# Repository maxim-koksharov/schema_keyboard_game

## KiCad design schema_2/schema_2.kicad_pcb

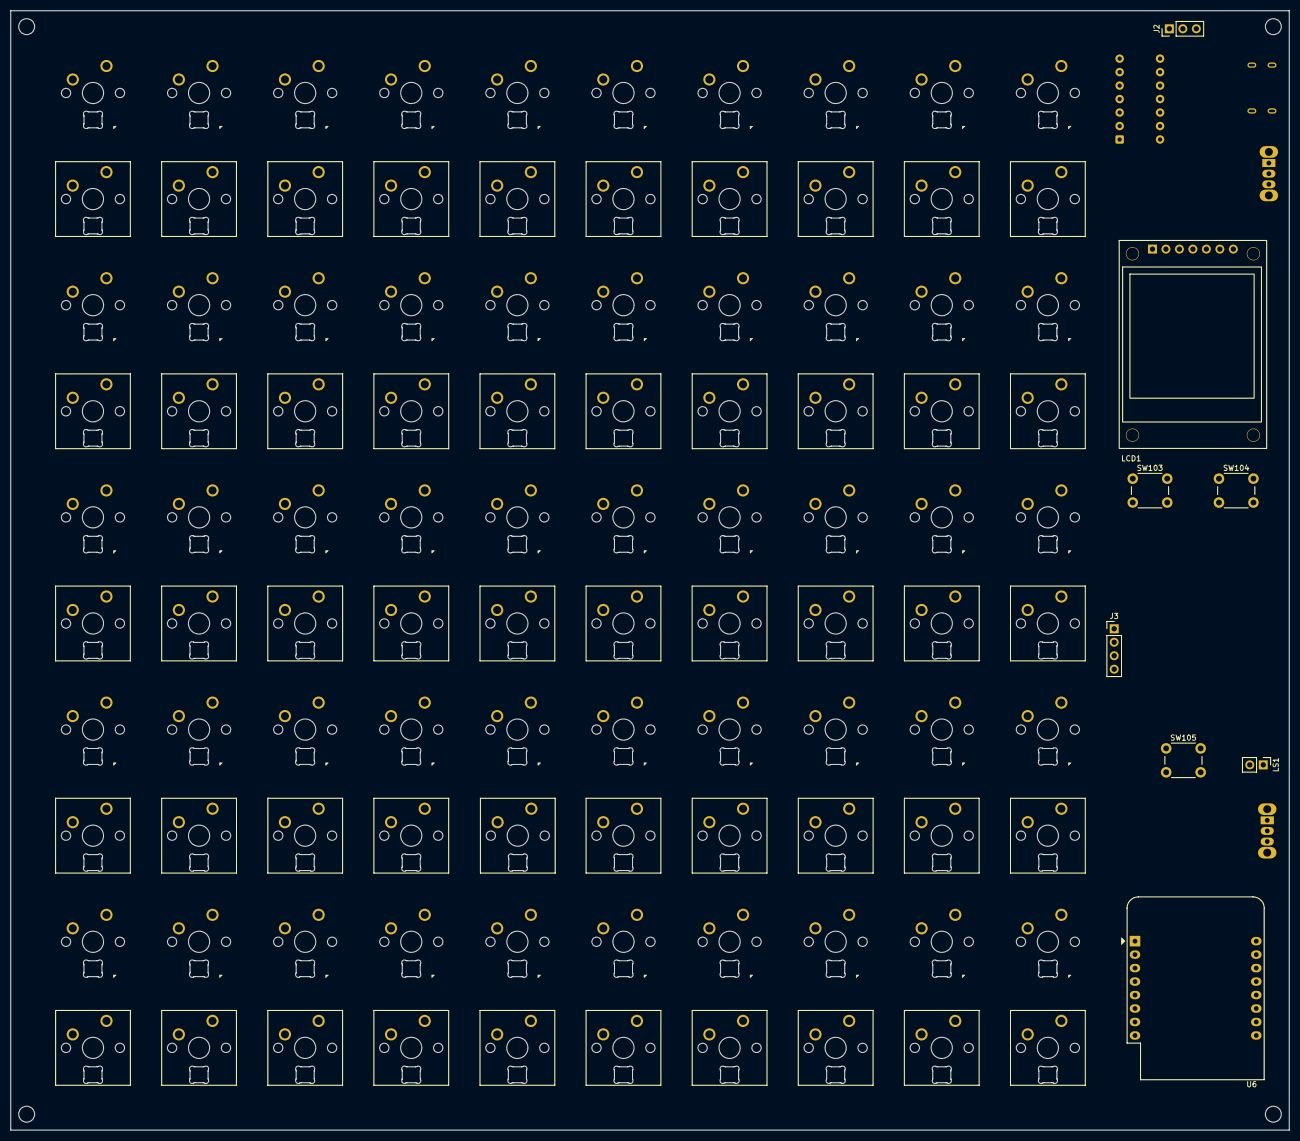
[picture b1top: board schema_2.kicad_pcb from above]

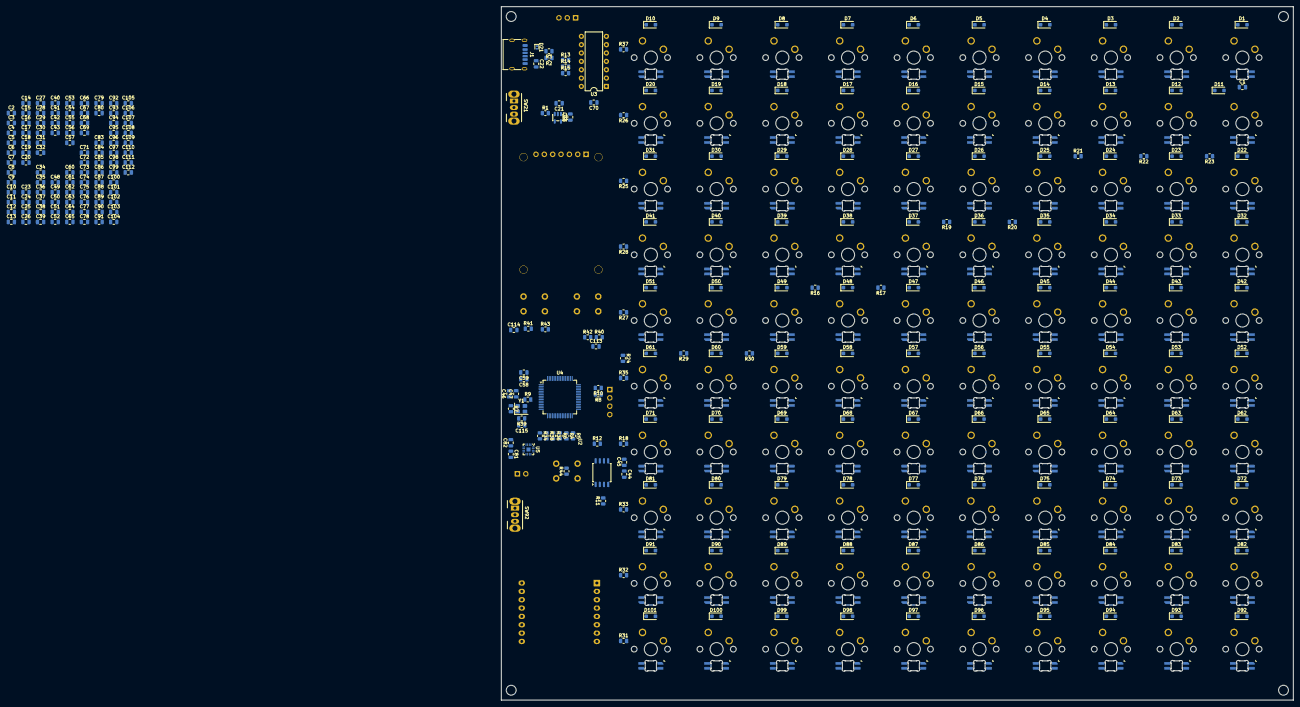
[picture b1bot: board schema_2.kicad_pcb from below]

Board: 2 copper layers, 241.0 x 211.0 mm, 377 parts (269 on the bottom side), 291 nets, no tracks yet.

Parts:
C1, C2, C3, C4, C5, C6, C7, C8, C9, C10, C11, C12, C13, C14, C15, C16, C17, C18, C19, C20, C22, C23, C24, C25, C26, C27, C28, C29, C30, C31, C32, C34, C35, C36, C37, C38, C39, C40, C41, C42, C43, C45, C47, C48, C49, C50, C51, C52, C53, C54, C55, C56, C57, C58, C60, C61, C62, C63, C64, C65, C66, C67, C68, C69, C71, C72, C73, C74, C75, C76, C77, C78, C79, C80, C82, C83, C84, C85, C86, C87, C88, C89, C90, C91, C92, C93, C94, C95, C96, C97, C98, C99, C100, C101, C102, C103, C104, C105, C106, C107, C108, C109, C110, C111, C112, C113, C114, C115: 100n; C_0805_2012Metric
C21, C33: 1u; C_0805_2012Metric
C44, C46, C81: 10u; C_0805_2012Metric
C59: 4.7u; C_0805_2012Metric
C70: 100p; C_0805_2012Metric
D1, D2, D3, D4, D5, D6, D7, D8, D9, D10, D11, D12, D13, D14, D15, D16, D17, D18, D19, D20, D22, D23, D24, D25, D26, D27, D28, D29, D30, D31, D32, D33, D34, D35, D36, D37, D38, D39, D40, D41, D42, D43, D44, D45, D46, D47, D48, D49, D50, D51, D52, D53, D54, D55, D56, D57, D58, D59, D60, D61, D62, D63, D64, D65, D66, D67, D68, D69, D70, D71, D72, D73, D74, D75, D76, D77, D78, D79, D80, D81, D82, D83, D84, D85, D86, D87, D88, D89, D90, D91, D92, D93, D94, D95, D96, D97, D98, D99, D100, D101: SM4007PL; D_SOD-123F
D21: H5VL10B; D_SOD-882D
J1: USB_C_Receptacle_PowerOnly_6P; USB_C_Receptacle_HRO_TYPE-C-31-M-17
J2: Conn_01x03_Pin; PinHeader_1x03_P2.54mm_Vertical
J3: Conn_01x04_Pin; PinHeader_1x04_P2.54mm_Vertical
LCD1: ST7789_1.3_240x240_LCD_Module
LS1: Speaker; PinHeader_1x02_P2.54mm_Vertical
R1, R42, R43, R44: 1k; R_0805_2012Metric
R2, R3, R13, R14, R15: 5.1k; R_0805_2012Metric
R4, R5, R6, R8, R9, R10, R34, R36, R38: 22; R_0805_2012Metric
R7, R11, R12, R39, R40, R41: 10k; R_0805_2012Metric
R16, R17, R18, R19, R20, R21, R22, R23, R24, R25, R26, R27, R28, R29, R30, R31, R32, R33, R35, R37: 220; R_0805_2012Metric
SW1, SW2, SW3, SW4, SW5, SW6, SW7, SW8, SW9, SW10, SW22, SW23, SW24, SW25, SW26, SW27, SW28, SW29, SW30, SW31, SW42, SW43, SW44, SW45, SW46, SW47, SW48, SW49, SW50, SW51, SW62, SW63, SW64, SW65, SW66, SW67, SW68, SW69, SW70, SW71, SW82, SW83, SW84, SW85, SW86, SW87, SW88, SW89, SW90, SW91: SW_MX_1u_SK6812MINI-E
SW11, SW12, SW13, SW14, SW15, SW16, SW17, SW18, SW19, SW20, SW32, SW33, SW34, SW35, SW36, SW37, SW38, SW39, SW40, SW41, SW52, SW53, SW54, SW55, SW56, SW57, SW58, SW59, SW60, SW61, SW72, SW73, SW74, SW75, SW76, SW77, SW78, SW79, SW80, SW81, SW93, SW94, SW95, SW96, SW97, SW98, SW99, SW100, SW101, SW102: SW_MX_1u_SK6812MINI-E_ROTATE
SW21, SW92: SK12D07VG3; SW_Slide_SPDT_Angled_CK_OS102011MA1Q
SW103, SW104, SW105: SW_Push; SW_PUSH_6mm
U1: AP2112K-3.3; SOT-23-5
U2: W25Q128JVS; SOIC-8_5.3x5.3mm_P1.27mm
U3: 74AHCT125; DIP-14_W7.62mm
U4: STM32G070RBTx; LQFP-64_10x10mm_P0.5mm
U5: MAX98357A; TQFN-16-1EP_3x3mm_P0.5mm_EP1.23x1.23mm
U6: WEMOS_D1_mini; WEMOS_D1_mini_light
Y1: SX3M8.000M20F30TNN; Crystal_SMD_3225-4Pin_3.2x2.5mm

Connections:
+3V3: C33.1, C44.1, C45.1, C46.1, C47.1, C58.1, C59.1, J2.2, J3.3, LCD1.2 (VCC), R7.1, R11.1, R12.1, R39.2, R40.2, R41.2, U1.5 (VOUT), U2.8 (VCC), U4.8 (VDD), Y1.4 (VDD)
+5V: C21.1, C70.2, C81.1, C82.1, R1.1, SW21.1 (A), U1.1 (VIN), U3.14 (VCC), U5.7 (VDD), U5.8 (VDD)
+5VP: C1.1, C2.1, C3.1, C4.1, C5.1, C6.1, C7.1, C8.1, C9.1, C10.1, C11.1, C12.1, C13.1, C14.1, C15.1, C16.1, C17.1, C18.1, C19.1, C20.1, C22.1, C23.1, C24.1, C25.1, C26.1, C27.1, C28.1, C29.1, C30.1, C31.1, C32.1, C34.1, C35.1, C36.1, C37.1, C38.1, C39.1, C40.1, C41.1, C42.1, C43.1, C48.1, C49.1, C50.1, C51.1, C52.1, C53.1, C54.1, C55.1, C56.1, C57.1, C60.1, C61.1, C62.1, C63.1, C64.1, C65.1, C66.1, C67.1, C68.1, C69.1, C71.1, C72.1, C73.1, C74.1, C75.1, C76.1, C77.1, C78.1, C79.1, C80.1, C83.1, C84.1, C85.1, C86.1, C87.1, C88.1, C89.1, C90.1, C91.1, C92.1, C93.1, C94.1, C95.1, C96.1, C97.1, C98.1, C99.1, C100.1, C101.1, C102.1, C103.1, C104.1, C105.1, C106.1, C107.1, C108.1, C109.1, C110.1, C111.1, C112.1, D21.2 (A2), J1.A9 (VBUS), J1.B9 (VBUS), J2.1, R13.1, R14.1, R15.1, SW1.1 (VDD), SW2.1 (VDD), SW3.1 (VDD), SW4.1 (VDD), SW5.1 (VDD), SW6.1 (VDD), SW7.1 (VDD), SW8.1 (VDD), SW9.1 (VDD), SW10.1 (VDD), SW11.1 (VDD), SW12.1 (VDD), SW13.1 (VDD), SW14.1 (VDD), SW15.1 (VDD), SW16.1 (VDD), SW17.1 (VDD), SW18.1 (VDD), SW19.1 (VDD), SW20.1 (VDD), SW21.2 (B), SW22.1 (VDD), SW23.1 (VDD), SW24.1 (VDD), SW25.1 (VDD), SW26.1 (VDD), SW27.1 (VDD), SW28.1 (VDD), SW29.1 (VDD), SW30.1 (VDD), SW31.1 (VDD), SW32.1 (VDD), SW33.1 (VDD), SW34.1 (VDD), SW35.1 (VDD), SW36.1 (VDD), SW37.1 (VDD), SW38.1 (VDD), SW39.1 (VDD), SW40.1 (VDD), SW41.1 (VDD), SW42.1 (VDD), SW43.1 (VDD), SW44.1 (VDD), SW45.1 (VDD), SW46.1 (VDD), SW47.1 (VDD), SW48.1 (VDD), SW49.1 (VDD), SW50.1 (VDD), SW51.1 (VDD), SW52.1 (VDD), SW53.1 (VDD), SW54.1 (VDD), SW55.1 (VDD), SW56.1 (VDD), SW57.1 (VDD), SW58.1 (VDD), SW59.1 (VDD), SW60.1 (VDD), SW61.1 (VDD), SW62.1 (VDD), SW63.1 (VDD), SW64.1 (VDD), SW65.1 (VDD), SW66.1 (VDD), SW67.1 (VDD), SW68.1 (VDD), SW69.1 (VDD), SW70.1 (VDD), SW71.1 (VDD), SW72.1 (VDD), SW73.1 (VDD), SW74.1 (VDD), SW75.1 (VDD), SW76.1 (VDD), SW77.1 (VDD), SW78.1 (VDD), SW79.1 (VDD), SW80.1 (VDD), SW81.1 (VDD), SW82.1 (VDD), SW83.1 (VDD), SW84.1 (VDD), SW85.1 (VDD), SW86.1 (VDD), SW87.1 (VDD), SW88.1 (VDD), SW89.1 (VDD), SW90.1 (VDD), SW91.1 (VDD), SW92.2 (B), SW93.1 (VDD), SW94.1 (VDD), SW95.1 (VDD), SW96.1 (VDD), SW97.1 (VDD), SW98.1 (VDD), SW99.1 (VDD), SW100.1 (VDD), SW101.1 (VDD), SW102.1 (VDD)
/audio_bclk: R36.1, U4.22 (PA5)
/audio_din: R34.1, U4.19 (PA2)
/audio_lrclk: R38.1, U4.21 (PA4)
/audio_mode: U4.23 (PA6), U5.4 (~SD_MODE)
/blk_lcd: LCD1.7 (BLK), U4.62 (PB8)
/col_1: D1.1 (K), D11.1 (K), D22.1 (K), D32.1 (K), D42.1 (K), D52.1 (K), D62.1 (K), D72.1 (K), D82.1 (K), D92.1 (K), R23.1
/col_2: D2.1 (K), D12.1 (K), D23.1 (K), D33.1 (K), D43.1 (K), D53.1 (K), D63.1 (K), D73.1 (K), D83.1 (K), D93.1 (K), R22.1
/col_3: D3.1 (K), D13.1 (K), D24.1 (K), D34.1 (K), D44.1 (K), D54.1 (K), D64.1 (K), D74.1 (K), D84.1 (K), D94.1 (K), R21.1
/col_4: D4.1 (K), D14.1 (K), D25.1 (K), D35.1 (K), D45.1 (K), D55.1 (K), D65.1 (K), D75.1 (K), D85.1 (K), D95.1 (K), R20.1
/col_5: D5.1 (K), D15.1 (K), D26.1 (K), D36.1 (K), D46.1 (K), D56.1 (K), D66.1 (K), D76.1 (K), D86.1 (K), D96.1 (K), R19.1
/col_6: D6.1 (K), D16.1 (K), D27.1 (K), D37.1 (K), D47.1 (K), D57.1 (K), D67.1 (K), D77.1 (K), D87.1 (K), D97.1 (K), R17.1
/col_7: D7.1 (K), D17.1 (K), D28.1 (K), D38.1 (K), D48.1 (K), D58.1 (K), D68.1 (K), D78.1 (K), D88.1 (K), D98.1 (K), R16.1
/col_8: D8.1 (K), D18.1 (K), D29.1 (K), D39.1 (K), D49.1 (K), D59.1 (K), D69.1 (K), D79.1 (K), D89.1 (K), D99.1 (K), R30.1
/col_9: D9.1 (K), D19.1 (K), D30.1 (K), D40.1 (K), D50.1 (K), D60.1 (K), D70.1 (K), D80.1 (K), D90.1 (K), D100.1 (K), R29.1
/col_10: D10.1 (K), D20.1 (K), D31.1 (K), D41.1 (K), D51.1 (K), D61.1 (K), D71.1 (K), D81.1 (K), D91.1 (K), D101.1 (K), R24.2
/dc_lcd: LCD1.6 (DC), U4.59 (PB5)
/esp_reset: U4.16 (PC3), U6.1 (~RST)
/esp_uart_rx: U4.17 (PA0), U6.15 (RX)
/esp_uart_tx: U4.18 (PA1), U6.16 (TX)
/key_1: C113.1, R40.1, R42.2, U4.1 (PC11)
/key_2: C114.1, R41.1, R43.2, U4.2 (PC12)
/led_1: SW9.4 (DIN), SW10.2 (DOUT)
/led_2: SW8.4 (DIN), SW9.2 (DOUT)
/led_3: SW7.4 (DIN), SW8.2 (DOUT)
/led_4: SW6.4 (DIN), SW7.2 (DOUT)
/led_5: SW5.4 (DIN), SW6.2 (DOUT)
/led_6: SW4.4 (DIN), SW5.2 (DOUT)
/led_7: SW3.4 (DIN), SW4.2 (DOUT)
/led_8: SW2.4 (DIN), SW3.2 (DOUT)
/led_9: SW1.4 (DIN), SW2.2 (DOUT)
/led_10: SW1.2 (DOUT), SW11.4 (DIN)
/led_11: SW11.2 (DOUT), SW12.4 (DIN)
/led_12: SW12.2 (DOUT), SW13.4 (DIN)
/led_13: SW13.2 (DOUT), SW14.4 (DIN)
/led_14: SW14.2 (DOUT), SW15.4 (DIN)
/led_15: SW15.2 (DOUT), SW16.4 (DIN)
/led_16: SW16.2 (DOUT), SW17.4 (DIN)
/led_17: SW17.2 (DOUT), SW18.4 (DIN)
/led_18: SW18.2 (DOUT), SW19.4 (DIN)
/led_19: SW19.2 (DOUT), SW20.4 (DIN)
/led_20: SW20.2 (DOUT), SW31.4 (DIN)
/led_21: SW30.4 (DIN), SW31.2 (DOUT)
/led_22: SW29.4 (DIN), SW30.2 (DOUT)
/led_23: SW28.4 (DIN), SW29.2 (DOUT)
/led_24: SW27.4 (DIN), SW28.2 (DOUT)
/led_25: SW26.4 (DIN), SW27.2 (DOUT)
/led_26: SW25.4 (DIN), SW26.2 (DOUT)
/led_27: SW24.4 (DIN), SW25.2 (DOUT)
/led_28: SW23.4 (DIN), SW24.2 (DOUT)
/led_29: SW22.4 (DIN), SW23.2 (DOUT)
/led_30: SW22.2 (DOUT), SW32.4 (DIN)
/led_31: SW32.2 (DOUT), SW33.4 (DIN)
/led_32: SW33.2 (DOUT), SW34.4 (DIN)
/led_33: SW34.2 (DOUT), SW35.4 (DIN)
/led_34: SW35.2 (DOUT), SW36.4 (DIN)
/led_35: SW36.2 (DOUT), SW37.4 (DIN)
/led_36: SW37.2 (DOUT), SW38.4 (DIN)
/led_37: SW38.2 (DOUT), SW39.4 (DIN)
/led_38: SW39.2 (DOUT), SW40.4 (DIN)
/led_39: SW40.2 (DOUT), SW41.4 (DIN)
/led_40: SW41.2 (DOUT), SW51.4 (DIN)
/led_41: SW50.4 (DIN), SW51.2 (DOUT)
/led_42: SW49.4 (DIN), SW50.2 (DOUT)
/led_43: SW48.4 (DIN), SW49.2 (DOUT)
/led_44: SW47.4 (DIN), SW48.2 (DOUT)
/led_45: SW46.4 (DIN), SW47.2 (DOUT)
/led_46: SW45.4 (DIN), SW46.2 (DOUT)
/led_47: SW44.4 (DIN), SW45.2 (DOUT)
/led_48: SW43.4 (DIN), SW44.2 (DOUT)
/led_49: SW42.4 (DIN), SW43.2 (DOUT)
/led_50: SW42.2 (DOUT), SW52.4 (DIN)
/led_51: SW52.2 (DOUT), SW53.4 (DIN)
/led_52: SW53.2 (DOUT), SW54.4 (DIN)
/led_53: SW54.2 (DOUT), SW55.4 (DIN)
/led_54: SW55.2 (DOUT), SW56.4 (DIN)
/led_55: SW56.2 (DOUT), SW57.4 (DIN)
/led_56: SW57.2 (DOUT), SW58.4 (DIN)
/led_57: SW58.2 (DOUT), SW59.4 (DIN)
/led_58: SW59.2 (DOUT), SW60.4 (DIN)
/led_59: SW60.2 (DOUT), SW61.4 (DIN)
/led_60: SW61.2 (DOUT), SW71.4 (DIN)
/led_61: SW70.4 (DIN), SW71.2 (DOUT)
/led_62: SW69.4 (DIN), SW70.2 (DOUT)
/led_63: SW68.4 (DIN), SW69.2 (DOUT)
/led_64: SW67.4 (DIN), SW68.2 (DOUT)
/led_65: SW66.4 (DIN), SW67.2 (DOUT)
/led_66: SW65.4 (DIN), SW66.2 (DOUT)
/led_67: SW64.4 (DIN), SW65.2 (DOUT)
/led_68: SW63.4 (DIN), SW64.2 (DOUT)
/led_69: SW62.4 (DIN), SW63.2 (DOUT)
/led_70: SW62.2 (DOUT), SW72.4 (DIN)
/led_71: SW72.2 (DOUT), SW73.4 (DIN)
/led_72: SW73.2 (DOUT), SW74.4 (DIN)
/led_73: SW74.2 (DOUT), SW75.4 (DIN)
/led_74: SW75.2 (DOUT), SW76.4 (DIN)
/led_75: SW76.2 (DOUT), SW77.4 (DIN)
/led_76: SW77.2 (DOUT), SW78.4 (DIN)
/led_77: SW78.2 (DOUT), SW79.4 (DIN)
/led_78: SW79.2 (DOUT), SW80.4 (DIN)
/led_79: SW80.2 (DOUT), SW81.4 (DIN)
/led_80: SW81.2 (DOUT), SW91.4 (DIN)
/led_81: SW90.4 (DIN), SW91.2 (DOUT)
/led_82: SW89.4 (DIN), SW90.2 (DOUT)
/led_83: SW88.4 (DIN), SW89.2 (DOUT)
/led_84: SW87.4 (DIN), SW88.2 (DOUT)
/led_85: SW86.4 (DIN), SW87.2 (DOUT)
/led_86: SW85.4 (DIN), SW86.2 (DOUT)
/led_87: SW84.4 (DIN), SW85.2 (DOUT)
/led_88: SW83.4 (DIN), SW84.2 (DOUT)
/led_89: SW82.4 (DIN), SW83.2 (DOUT)
/led_90: SW82.2 (DOUT), SW93.4 (DIN)
/led_91: SW93.2 (DOUT), SW94.4 (DIN)
/led_92: SW94.2 (DOUT), SW95.4 (DIN)
/led_93: SW95.2 (DOUT), SW96.4 (DIN)
/led_94: SW96.2 (DOUT), SW97.4 (DIN)
/led_95: SW97.2 (DOUT), SW98.4 (DIN)
/led_96: SW98.2 (DOUT), SW99.4 (DIN)
/led_97: SW99.2 (DOUT), SW100.4 (DIN)
/led_98: SW100.2 (DOUT), SW101.4 (DIN)
/led_99: SW101.2 (DOUT), SW102.4 (DIN)
/mcu_clk: R9.2, U4.10 (PF0)
/reset_lcd: LCD1.5 (RES), U4.58 (PB4)
/rgb_data_3V: U3.2, U4.64 (PC10)
/rgb_data_5V: SW10.4 (DIN), U3.3
/row_1: R37.2, SW1.5 (SW_1), SW2.5 (SW_1), SW3.5 (SW_1), SW4.5 (SW_1), SW5.5 (SW_1), SW6.5 (SW_1), SW7.5 (SW_1), SW8.5 (SW_1), SW9.5 (SW_1), SW10.5 (SW_1)
/row_2: R26.1, SW11.5 (SW_1), SW12.5 (SW_1), SW13.5 (SW_1), SW14.5 (SW_1), SW15.5 (SW_1), SW16.5 (SW_1), SW17.5 (SW_1), SW18.5 (SW_1), SW19.5 (SW_1), SW20.5 (SW_1)
/row_3: R25.1, SW22.5 (SW_1), SW23.5 (SW_1), SW24.5 (SW_1), SW25.5 (SW_1), SW26.5 (SW_1), SW27.5 (SW_1), SW28.5 (SW_1), SW29.5 (SW_1), SW30.5 (SW_1), SW31.5 (SW_1)
/row_4: R28.1, SW32.5 (SW_1), SW33.5 (SW_1), SW34.5 (SW_1), SW35.5 (SW_1), SW36.5 (SW_1), SW37.5 (SW_1), SW38.5 (SW_1), SW39.5 (SW_1), SW40.5 (SW_1), SW41.5 (SW_1)
/row_5: R27.1, SW42.5 (SW_1), SW43.5 (SW_1), SW44.5 (SW_1), SW45.5 (SW_1), SW46.5 (SW_1), SW47.5 (SW_1), SW48.5 (SW_1), SW49.5 (SW_1), SW50.5 (SW_1), SW51.5 (SW_1)
/row_6: R35.2, SW52.5 (SW_1), SW53.5 (SW_1), SW54.5 (SW_1), SW55.5 (SW_1), SW56.5 (SW_1), SW57.5 (SW_1), SW58.5 (SW_1), SW59.5 (SW_1), SW60.5 (SW_1), SW61.5 (SW_1)
/row_7: R18.2, SW62.5 (SW_1), SW63.5 (SW_1), SW64.5 (SW_1), SW65.5 (SW_1), SW66.5 (SW_1), SW67.5 (SW_1), SW68.5 (SW_1), SW69.5 (SW_1), SW70.5 (SW_1), SW71.5 (SW_1)
/row_8: R33.2, SW72.5 (SW_1), SW73.5 (SW_1), SW74.5 (SW_1), SW75.5 (SW_1), SW76.5 (SW_1), SW77.5 (SW_1), SW78.5 (SW_1), SW79.5 (SW_1), SW80.5 (SW_1), SW81.5 (SW_1)
/row_9: R32.2, SW82.5 (SW_1), SW83.5 (SW_1), SW84.5 (SW_1), SW85.5 (SW_1), SW86.5 (SW_1), SW87.5 (SW_1), SW88.5 (SW_1), SW89.5 (SW_1), SW90.5 (SW_1), SW91.5 (SW_1)
/row_10: R31.2, SW93.5 (SW_1), SW94.5 (SW_1), SW95.5 (SW_1), SW96.5 (SW_1), SW97.5 (SW_1), SW98.5 (SW_1), SW99.5 (SW_1), SW100.5 (SW_1), SW101.5 (SW_1), SW102.5 (SW_1)
/spi_clk_lcd: LCD1.3 (SCK), U4.57 (PB3)
/spi_data_lcd: LCD1.4 (SDA), U4.60 (PB6)
/spi_mem_clk: R4.1, U4.30 (PB10)
/spi_mem_cs: U2.1 (~CS), U4.32 (PB12)
/spi_mem_miso: R6.1, U4.29 (PB2)
/spi_mem_mosi: R5.1, U4.31 (PB11)
/stm32_reset: C115.1, R39.1, R44.2, U4.12 (NRST)
/swclk: R10.2, U4.46 (PA14)
/swdio: R8.2, U4.45 (PA13)
GND: C1.2, C2.2, C3.2, C4.2, C5.2, C6.2, C7.2, C8.2, C9.2, C10.2, C11.2, C12.2, C13.2, C14.2, C15.2, C16.2, C17.2, C18.2, C19.2, C20.2, C21.2, C22.2, C23.2, C24.2, C25.2, C26.2, C27.2, C28.2, C29.2, C30.2, C31.2, C32.2, C33.2, C34.2, C35.2, C36.2, C37.2, C38.2, C39.2, C40.2, C41.2, C42.2, C43.2, C44.2, C45.2, C46.2, C47.2, C48.2, C49.2, C50.2, C51.2, C52.2, C53.2, C54.2, C55.2, C56.2, C57.2, C58.2, C59.2, C60.2, C61.2, C62.2, C63.2, C64.2, C65.2, C66.2, C67.2, C68.2, C69.2, C70.1, C71.2, C72.2, C73.2, C74.2, C75.2, C76.2, C77.2, C78.2, C79.2, C80.2, C81.2, C82.2, C83.2, C84.2, C85.2, C86.2, C87.2, C88.2, C89.2, C90.2, C91.2, C92.2, C93.2, C94.2, C95.2, C96.2, C97.2, C98.2, C99.2, C100.2, C101.2, C102.2, C103.2, C104.2, C105.2, C106.2, C107.2, C108.2, C109.2, C110.2, C111.2, C112.2, C113.2, C114.2, C115.2, D21.1 (A1), J1.A12 (GND), J1.B12 (GND), J2.3, J3.4, LCD1.1 (GND), R2.1, R3.1, SW1.3 (VSS), SW2.3 (VSS), SW3.3 (VSS), SW4.3 (VSS), SW5.3 (VSS), SW6.3 (VSS), SW7.3 (VSS), SW8.3 (VSS), SW9.3 (VSS), SW10.3 (VSS), SW11.3 (VSS), SW12.3 (VSS), SW13.3 (VSS), SW14.3 (VSS), SW15.3 (VSS), SW16.3 (VSS), SW17.3 (VSS), SW18.3 (VSS), SW19.3 (VSS), SW20.3 (VSS), SW22.3 (VSS), SW23.3 (VSS), SW24.3 (VSS), SW25.3 (VSS), SW26.3 (VSS), SW27.3 (VSS), SW28.3 (VSS), SW29.3 (VSS), SW30.3 (VSS), SW31.3 (VSS), SW32.3 (VSS), SW33.3 (VSS), SW34.3 (VSS), SW35.3 (VSS), SW36.3 (VSS), SW37.3 (VSS), SW38.3 (VSS), SW39.3 (VSS), SW40.3 (VSS), SW41.3 (VSS), SW42.3 (VSS), SW43.3 (VSS), SW44.3 (VSS), SW45.3 (VSS), SW46.3 (VSS), SW47.3 (VSS), SW48.3 (VSS), SW49.3 (VSS), SW50.3 (VSS), SW51.3 (VSS), SW52.3 (VSS), SW53.3 (VSS), SW54.3 (VSS), SW55.3 (VSS), SW56.3 (VSS), SW57.3 (VSS), SW58.3 (VSS), SW59.3 (VSS), SW60.3 (VSS), SW61.3 (VSS), SW62.3 (VSS), SW63.3 (VSS), SW64.3 (VSS), SW65.3 (VSS), SW66.3 (VSS), SW67.3 (VSS), SW68.3 (VSS), SW69.3 (VSS), SW70.3 (VSS), SW71.3 (VSS), SW72.3 (VSS), SW73.3 (VSS), SW74.3 (VSS), SW75.3 (VSS), SW76.3 (VSS), SW77.3 (VSS), SW78.3 (VSS), SW79.3 (VSS), SW80.3 (VSS), SW81.3 (VSS), SW82.3 (VSS), SW83.3 (VSS), SW84.3 (VSS), SW85.3 (VSS), SW86.3 (VSS), SW87.3 (VSS), SW88.3 (VSS), SW89.3 (VSS), SW90.3 (VSS), SW91.3 (VSS), SW93.3 (VSS), SW94.3 (VSS), SW95.3 (VSS), SW96.3 (VSS), SW97.3 (VSS), SW98.3 (VSS), SW99.3 (VSS), SW100.3 (VSS), SW101.3 (VSS), SW102.3 (VSS), SW103.1, SW104.1, SW105.1, U1.2 (GND), U2.4 (GND), U3.1, U3.7 (GND), U4.9 (VSS), U5.2 (GAIN_SLOT), U5.3 (GND), U5.11 (GND), U5.15 (GND), U5.17 (PAD), U6.10 (GND), Y1.2 (GND)
unnamed: D1.2 (A), SW1.6 (SW_2)
unnamed: D2.2 (A), SW2.6 (SW_2)
unnamed: D3.2 (A), SW3.6 (SW_2)
unnamed: D4.2 (A), SW4.6 (SW_2)
unnamed: D5.2 (A), SW5.6 (SW_2)
unnamed: D6.2 (A), SW6.6 (SW_2)
unnamed: D7.2 (A), SW7.6 (SW_2)
unnamed: D8.2 (A), SW8.6 (SW_2)
unnamed: D9.2 (A), SW9.6 (SW_2)
unnamed: D10.2 (A), SW10.6 (SW_2)
unnamed: D11.2 (A), SW11.6 (SW_2)
unnamed: D12.2 (A), SW12.6 (SW_2)
unnamed: D13.2 (A), SW13.6 (SW_2)
unnamed: D14.2 (A), SW14.6 (SW_2)
unnamed: D15.2 (A), SW15.6 (SW_2)
unnamed: D16.2 (A), SW16.6 (SW_2)
unnamed: D17.2 (A), SW17.6 (SW_2)
unnamed: D18.2 (A), SW18.6 (SW_2)
unnamed: D19.2 (A), SW19.6 (SW_2)
unnamed: D20.2 (A), SW20.6 (SW_2)
unnamed: D22.2 (A), SW22.6 (SW_2)
unnamed: D23.2 (A), SW23.6 (SW_2)
unnamed: D24.2 (A), SW24.6 (SW_2)
unnamed: D25.2 (A), SW25.6 (SW_2)
unnamed: D26.2 (A), SW26.6 (SW_2)
unnamed: D27.2 (A), SW27.6 (SW_2)
unnamed: D28.2 (A), SW28.6 (SW_2)
unnamed: D29.2 (A), SW29.6 (SW_2)
unnamed: D30.2 (A), SW30.6 (SW_2)
unnamed: D31.2 (A), SW31.6 (SW_2)
unnamed: D32.2 (A), SW32.6 (SW_2)
unnamed: D33.2 (A), SW33.6 (SW_2)
unnamed: D34.2 (A), SW34.6 (SW_2)
unnamed: D35.2 (A), SW35.6 (SW_2)
unnamed: D36.2 (A), SW36.6 (SW_2)
unnamed: D37.2 (A), SW37.6 (SW_2)
unnamed: D38.2 (A), SW38.6 (SW_2)
unnamed: D39.2 (A), SW39.6 (SW_2)
unnamed: D40.2 (A), SW40.6 (SW_2)
unnamed: D41.2 (A), SW41.6 (SW_2)
unnamed: D42.2 (A), SW42.6 (SW_2)
unnamed: D43.2 (A), SW43.6 (SW_2)
unnamed: D44.2 (A), SW44.6 (SW_2)
unnamed: D45.2 (A), SW45.6 (SW_2)
unnamed: D46.2 (A), SW46.6 (SW_2)
unnamed: D47.2 (A), SW47.6 (SW_2)
unnamed: D48.2 (A), SW48.6 (SW_2)
unnamed: D49.2 (A), SW49.6 (SW_2)
unnamed: D50.2 (A), SW50.6 (SW_2)
unnamed: D51.2 (A), SW51.6 (SW_2)
unnamed: D52.2 (A), SW52.6 (SW_2)
unnamed: D53.2 (A), SW53.6 (SW_2)
unnamed: D54.2 (A), SW54.6 (SW_2)
unnamed: D55.2 (A), SW55.6 (SW_2)
unnamed: D56.2 (A), SW56.6 (SW_2)
unnamed: D57.2 (A), SW57.6 (SW_2)
unnamed: D58.2 (A), SW58.6 (SW_2)
unnamed: D59.2 (A), SW59.6 (SW_2)
unnamed: D60.2 (A), SW60.6 (SW_2)
unnamed: D61.2 (A), SW61.6 (SW_2)
unnamed: D62.2 (A), SW62.6 (SW_2)
unnamed: D63.2 (A), SW63.6 (SW_2)
unnamed: D64.2 (A), SW64.6 (SW_2)
unnamed: D65.2 (A), SW65.6 (SW_2)
unnamed: D66.2 (A), SW66.6 (SW_2)
unnamed: D67.2 (A), SW67.6 (SW_2)
unnamed: D68.2 (A), SW68.6 (SW_2)
unnamed: D69.2 (A), SW69.6 (SW_2)
unnamed: D70.2 (A), SW70.6 (SW_2)
unnamed: D71.2 (A), SW71.6 (SW_2)
unnamed: D72.2 (A), SW72.6 (SW_2)
unnamed: D73.2 (A), SW73.6 (SW_2)
unnamed: D74.2 (A), SW74.6 (SW_2)
unnamed: D75.2 (A), SW75.6 (SW_2)
unnamed: D76.2 (A), SW76.6 (SW_2)
unnamed: D77.2 (A), SW77.6 (SW_2)
unnamed: D78.2 (A), SW78.6 (SW_2)
unnamed: D79.2 (A), SW79.6 (SW_2)
unnamed: D80.2 (A), SW80.6 (SW_2)
unnamed: D81.2 (A), SW81.6 (SW_2)
unnamed: D82.2 (A), SW82.6 (SW_2)
unnamed: D83.2 (A), SW83.6 (SW_2)
unnamed: D84.2 (A), SW84.6 (SW_2)
unnamed: D85.2 (A), SW85.6 (SW_2)
unnamed: D86.2 (A), SW86.6 (SW_2)
unnamed: D87.2 (A), SW87.6 (SW_2)
unnamed: D88.2 (A), SW88.6 (SW_2)
unnamed: D89.2 (A), SW89.6 (SW_2)
unnamed: D90.2 (A), SW90.6 (SW_2)
unnamed: D91.2 (A), SW91.6 (SW_2)
unnamed: D92.2 (A), SW93.6 (SW_2)
unnamed: D93.2 (A), SW94.6 (SW_2)
unnamed: D94.2 (A), SW95.6 (SW_2)
unnamed: D95.2 (A), SW96.6 (SW_2)
unnamed: D96.2 (A), SW97.6 (SW_2)
unnamed: D97.2 (A), SW98.6 (SW_2)
unnamed: D98.2 (A), SW99.6 (SW_2)
unnamed: D99.2 (A), SW100.6 (SW_2)
unnamed: D100.2 (A), SW101.6 (SW_2)
unnamed: D101.2 (A), SW102.6 (SW_2)
unnamed: J1.A5 (CC1), R3.2
unnamed: J1.B5 (CC2), R2.2
unnamed: J3.1, R8.1
unnamed: J3.2, R10.1
unnamed: R13.2, U3.4, U3.5
unnamed: R14.2, U3.9, U3.10
unnamed: R15.2, U3.12, U3.13
unnamed: R42.1, SW103.2
unnamed: R43.1, SW104.2
unnamed: R44.1, SW105.2
unnamed: SW92.1 (A), U6.9 (5V)
unnamed: R1.2, U1.3 (EN)
unnamed: R4.2, U2.6 (CLK)
unnamed: R5.2, U2.5 (DI/IO_{0})
unnamed: R6.2, U2.2 (DO/IO_{1})
unnamed: R12.2, U2.7 (~HOLD/~RESET/IO_{3})
unnamed: R11.2, U2.3 (~WP/IO_{2})
unnamed: R18.1, U4.36 (PA8)
unnamed: R35.1, U4.37 (PA9)
unnamed: R37.1, U4.42 (PA10)
unnamed: R24.1, U4.47 (PA15)
unnamed: R31.1, U4.33 (PB13)
unnamed: R32.1, U4.34 (PB14)
unnamed: R33.1, U4.35 (PB15)
unnamed: R27.2, U4.38 (PC6)
unnamed: R28.2, U4.39 (PC7)
unnamed: R29.2, U4.48 (PC8)
unnamed: R30.2, U4.49 (PC9)
unnamed: R16.2, U4.50 (PD0)
unnamed: R17.2, U4.51 (PD1)
unnamed: R19.2, U4.52 (PD2)
unnamed: R20.2, U4.53 (PD3)
unnamed: R21.2, U4.54 (PD4)
unnamed: R22.2, U4.55 (PD5)
unnamed: R23.2, U4.56 (PD6)
unnamed: R25.2, U4.40 (PD8)
unnamed: R26.2, U4.41 (PD9)
unnamed: R36.2, U5.16 (BCLK)
unnamed: R34.2, U5.1 (DIN)
unnamed: R38.2, U5.14 (LRCLK)
unnamed: LS1.2, U5.10 (OUTN)
unnamed: LS1.1, U5.9 (OUTP)
unnamed: R9.1, Y1.3 (OUT)
unnamed: R7.2, Y1.1 (Tri-State)
